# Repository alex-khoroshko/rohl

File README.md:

# Reef open hardware light
This is a project of open source / open hardware reef light. Current stage of development - proof of concept.

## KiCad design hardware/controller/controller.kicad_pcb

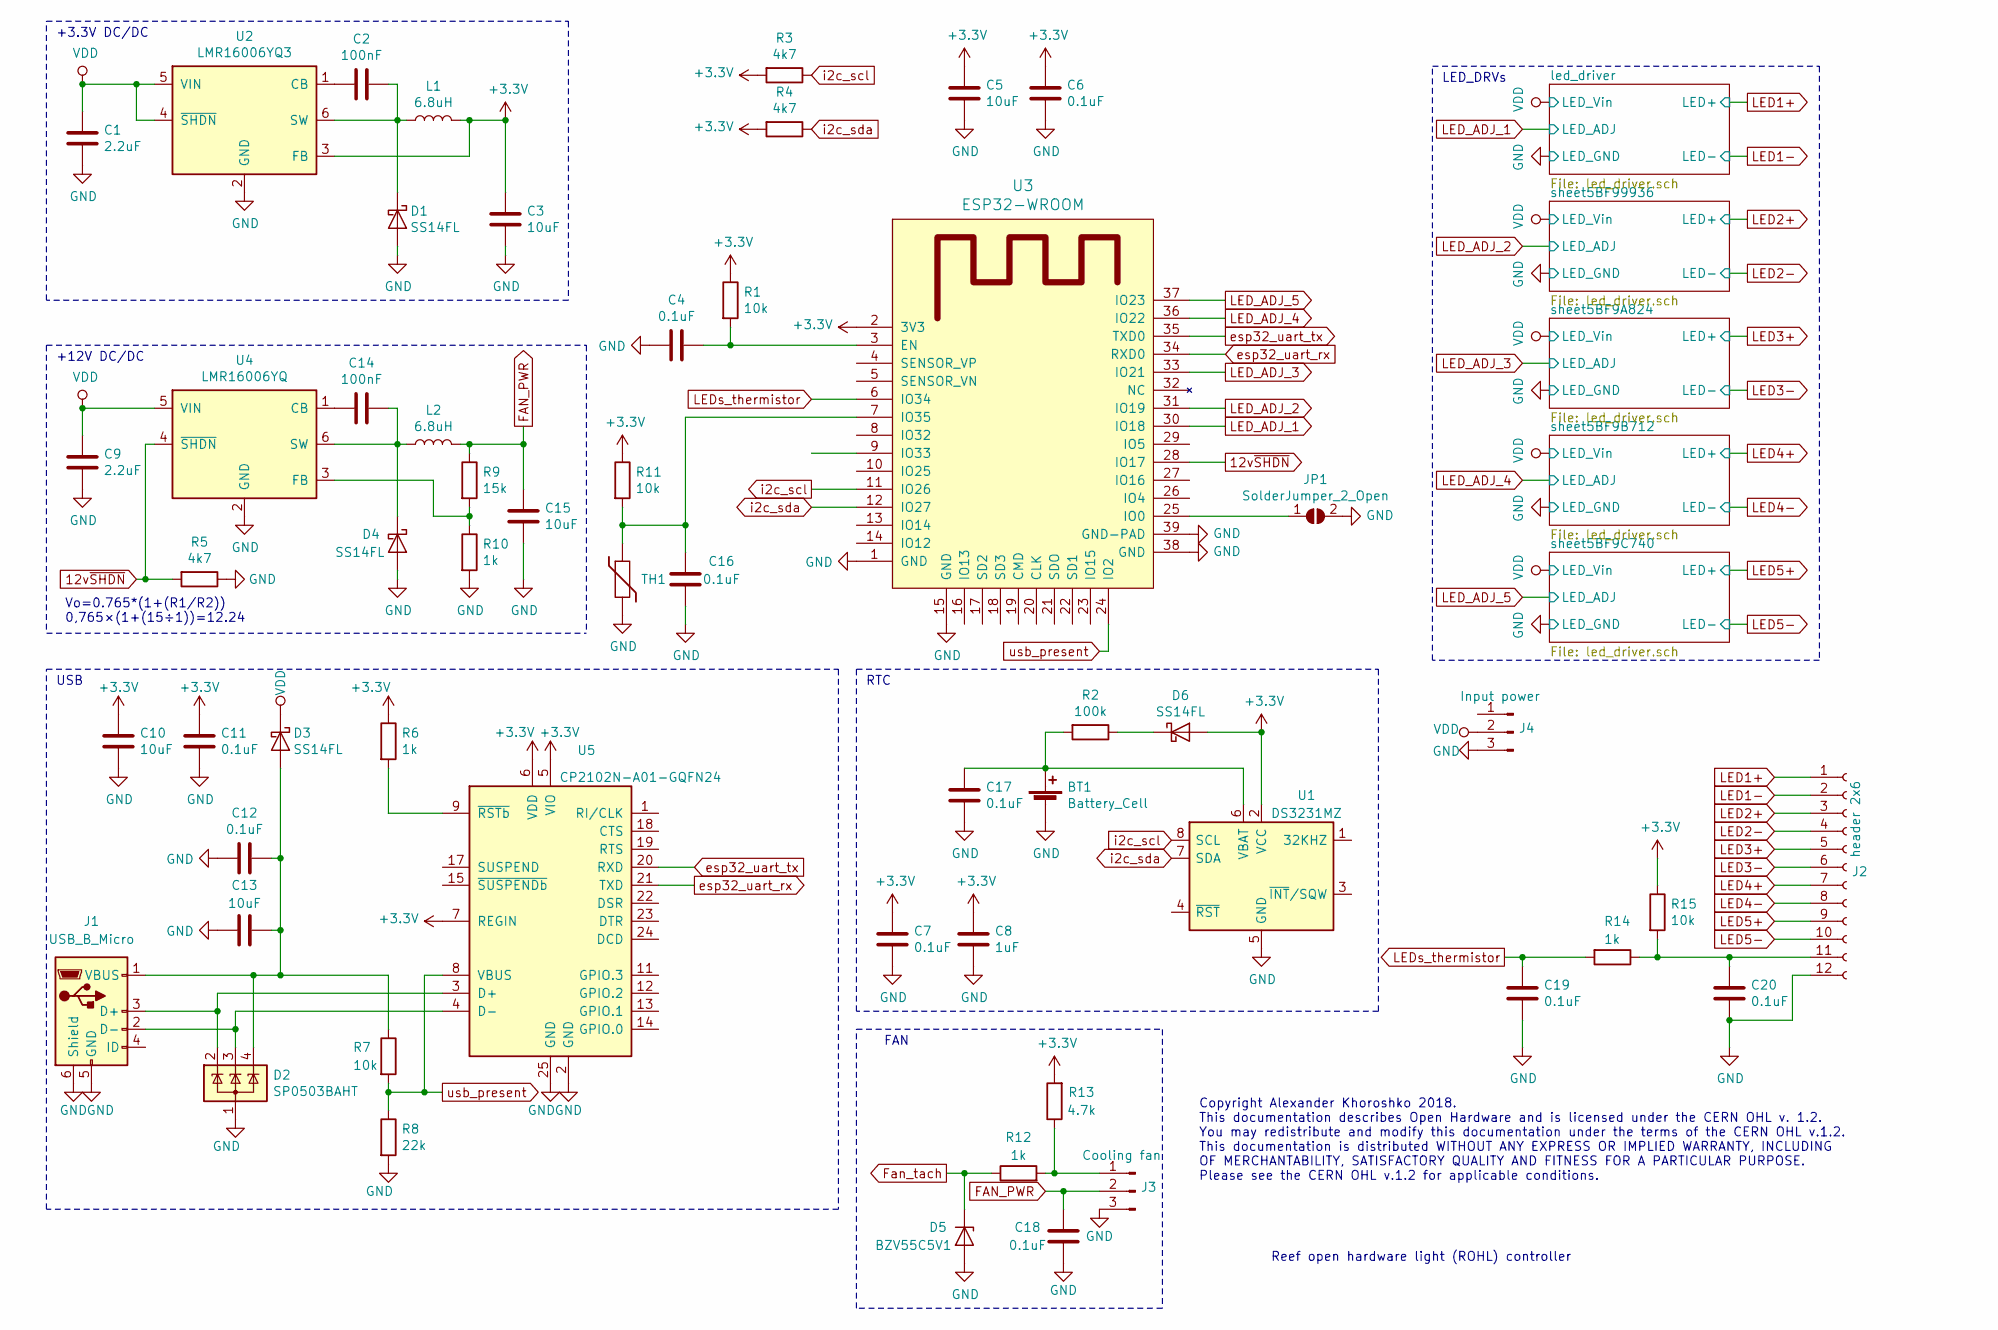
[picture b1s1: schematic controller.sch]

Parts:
BT1: Battery_Cell; MS621FE-FL11E
C1, C9: 2.2uF; C_0603_1608Metric_Pad1.05x0.95mm_HandSolder
C2, C14: 100nF; C_0603_1608Metric_Pad1.05x0.95mm_HandSolder
C3, C5, C10, C13, C15: 10uF; C_0603_1608Metric_Pad1.05x0.95mm_HandSolder
C4, C6, C7, C11, C12, C16, C17, C18, C19, C20: 0.1uF; C_0603_1608Metric_Pad1.05x0.95mm_HandSolder
C8: 1uF; C_0603_1608Metric_Pad1.05x0.95mm_HandSolder
D1, D3, D4, D6: SS14FL; D_SOD-123F
D2: SP0503BAHT; SOT-143
D5: BZV55C5V1; D_MiniMELF
J1: USB_B_Micro; USB_Micro-B_Molex-105017-0001
J2: header 2x6; PinHeader_2x06_P2.54mm_Vertical
J3: Cooling fan; FanPinHeader_1x03_P2.54mm_Vertical
J4: Input power; FanPinHeader_1x03_P2.54mm_Vertical
JP1: SolderJumper_2_Open; SolderJumper-2_P1.3mm_Open_TrianglePad1.0x1.5mm
L1, L2: 6.8uH; L_Wuerth_MAPI-3015
R1, R7, R11, R15: 10k; R_0603_1608Metric_Pad1.05x0.95mm_HandSolder
R2: 100k; R_0603_1608Metric_Pad1.05x0.95mm_HandSolder
R3, R4, R5: 4k7; R_0603_1608Metric_Pad1.05x0.95mm_HandSolder
R6, R10, R12, R14: 1k; R_0603_1608Metric_Pad1.05x0.95mm_HandSolder
R8: 22k; R_0603_1608Metric_Pad1.05x0.95mm_HandSolder
R9: 15k; R_0603_1608Metric_Pad1.05x0.95mm_HandSolder
R13: 4.7k; R_0603_1608Metric_Pad1.05x0.95mm_HandSolder
TH1: NTCS0603E3103; R_0603_1608Metric_Pad1.05x0.95mm_HandSolder
U1: DS3231MZ; SOIC-8_3.9x4.9mm_P1.27mm
U2: LMR16006YQ3; SOT-23-6
U3: ESP32-WROOM
U4: LMR16006YQ; SOT-23-6
U5: CP2102N-A01-GQFN24; QFN-24-1EP_4x4mm_P0.5mm_EP2.6x2.6mm

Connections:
12v~SHDN: R5.2, U3.28 (IO17), U4.4 (~SHDN)
+3V3: C3.1, C5.1, C6.2, C7.2, C8.2, C10.1, C11.2, D6.2 (A), L1.2, R1.1, R3.2, R4.2, R6.1, R11.1, R13.2, R15.1, U1.2 (VCC), U2.3 (FB), U3.2 (3V3), U5.5 (VIO), U5.6 (VDD), U5.7 (REGIN)
FAN_PWR: C15.1, C18.2, J3.2, L2.2, R9.1
Fan_tach: D5.1 (K), R12.1
GND: BT1.2 (-), C1.2, C3.2, C4.2, C5.2, C6.1, C7.1, C8.1, C9.2, C10.2, C11.1, C12.1, C13.2, C15.2, C16.1, C17.1, C18.1, C19.1, C20.1, D1.2 (A), D2.1 (A), D4.2 (A), D5.2 (A), J1.5 (GND), J1.6 (Shield), J2.12, J3.3, J4.3, JP1.2 (B), R5.1, R8.2, R10.2, TH1.2, U1.5 (GND), U2.2 (GND), U3.1 (GND), U3.15 (GND), U3.38 (GND), U3.39 (GND-PAD), U4.2 (GND), U5.2 (GND), U5.25 (GND); also elsewhere on the board
LED1+: J2.1; also elsewhere on the board
LED1-: J2.2; also elsewhere on the board
LED2+: J2.3; also elsewhere on the board
LED2-: J2.4; also elsewhere on the board
LED3+: J2.5; also elsewhere on the board
LED3-: J2.6; also elsewhere on the board
LED4+: J2.7; also elsewhere on the board
LED4-: J2.8; also elsewhere on the board
LED5+: J2.9; also elsewhere on the board
LED5-: J2.10; also elsewhere on the board
LED_ADJ_1: U3.30 (IO18); also elsewhere on the board
LED_ADJ_2: U3.31 (IO19); also elsewhere on the board
LED_ADJ_3: U3.33 (IO21); also elsewhere on the board
LED_ADJ_4: U3.36 (IO22); also elsewhere on the board
LED_ADJ_5: U3.37 (IO23); also elsewhere on the board
LEDs_thermistor: C19.2, R14.2, U3.6 (IO34)
unnamed: BT1.1 (+), C17.2, R2.2, U1.6 (VBAT)
unnamed: C2.1, D1.1 (K), L1.1, U2.6 (SW)
unnamed: C2.2, U2.1 (CB)
unnamed: C4.1, R1.2, U3.3 (EN)
unnamed: C12.2, C13.1, D2.4 (K), D3.2 (A), J1.1 (VBUS), R7.1
unnamed: C14.1, D4.1 (K), L2.1, U4.6 (SW)
unnamed: C14.2, U4.1 (CB)
unnamed: C16.2, R11.2, TH1.1, U3.7 (IO35)
unnamed: C20.2, J2.11, R14.1, R15.2
unnamed: D2.2 (K), J1.3 (D+), U5.3 (D+)
unnamed: D2.3 (K), J1.2 (D-), U5.4 (D-)
unnamed: D6.1 (K), R2.1
unnamed: J3.1, R12.2, R13.1
unnamed: JP1.1 (A), U3.25 (IO0)
unnamed: R6.2, U5.9 (~RSTb)
unnamed: R9.2, R10.1, U4.3 (FB)
VDD: C1.1, C9.1, D3.1 (K), J4.2, U2.4 (~SHDN), U2.5 (VIN), U4.5 (VIN); also elsewhere on the board
esp32_uart_rx: U3.34 (RXD0), U5.21 (TXD)
esp32_uart_tx: U3.35 (TXD0), U5.20 (RXD)
i2c_scl: R3.1, U1.8 (SCL), U3.11 (IO26)
i2c_sda: R4.1, U1.7 (SDA), U3.12 (IO27)
usb_present: R7.2, R8.1, U3.24 (IO2), U5.8 (VBUS)

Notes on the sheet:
RTC
+3.3V DC/DC
USB
LED_DRVs
+12V DC/DC
FAN
Vo=0.765*(1+(R1/R2)) 0,765×(1+(15÷1))=12.24
Copyright Alexander Khoroshko 2018. This documentation describes Open Hardware and is licensed under the CERN OHL v. 1.2. You may redistribute and modify this documentation under the terms of the CERN OHL v.1.2. This documentation is distributed WITHOUT ANY EXPRESS OR IMPLIED WARRANTY, INCLUDING OF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
Reef open hardware light (ROHL) controller

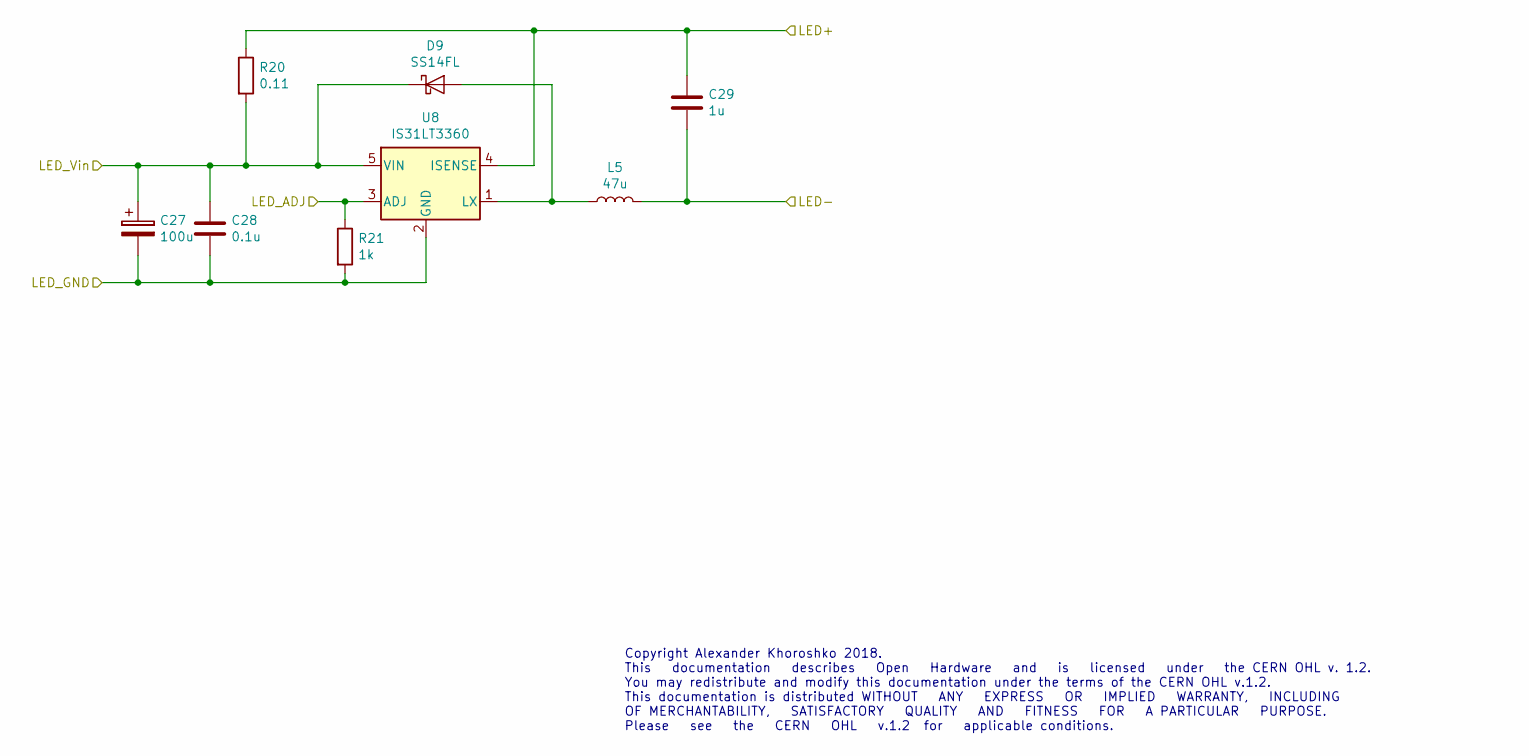
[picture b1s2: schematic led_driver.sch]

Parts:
C21: 100u; CP_Elec_10x7.9
C22: 0.1u; C_0603_1608Metric_Pad1.05x0.95mm_HandSolder
C23: 1u; C_0603_1608Metric_Pad1.05x0.95mm_HandSolder
D7: SS14FL; D_SOD-123F
L3: 47u; L_12x12mm_H6mm
R16: 0.11; R_0805_2012Metric_Pad1.15x1.40mm_HandSolder
R17: 1k; R_0603_1608Metric_Pad1.05x0.95mm_HandSolder
U6: IS31LT3360; SOT-89-5

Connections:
GND: C21.2, C22.2, R17.2, U6.2 (GND); also elsewhere on the board
LED1+: C23.1, R16.1, U6.4 (ISENSE); also elsewhere on the board
LED1-: C23.2, L3.2; also elsewhere on the board
LED_ADJ_1: R17.1, U6.3 (ADJ); also elsewhere on the board
unnamed: D7.2 (A), L3.1, U6.1 (LX)
VDD: C21.1, C22.1, D7.1 (K), R16.2, U6.5 (VIN); also elsewhere on the board

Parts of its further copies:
C24, C27, C30, C33: 100u; CP_Elec_10x7.9
C25, C28, C31, C34: 0.1u; C_0603_1608Metric_Pad1.05x0.95mm_HandSolder
C26, C29, C32, C35: 1u; C_0603_1608Metric_Pad1.05x0.95mm_HandSolder
D8, D9, D10, D11: SS14FL; D_SOD-123F
L4, L5, L6, L7: 47u; L_12x12mm_H6mm
R18, R20, R22, R24: 0.11; R_0805_2012Metric_Pad1.15x1.40mm_HandSolder
R19, R21, R23, R25: 1k; R_0603_1608Metric_Pad1.05x0.95mm_HandSolder
U7, U8, U9, U10: IS31LT3360; SOT-89-5

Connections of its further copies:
GND: C24.2, C25.2, C27.2, C28.2, C30.2, C31.2, C33.2, C34.2, R19.2, R21.2, R23.2, R25.2, U7.2 (GND), U8.2 (GND), U9.2 (GND), U10.2 (GND); also elsewhere on the board
LED2+: C26.1, R18.1, U7.4 (ISENSE); also elsewhere on the board
LED2-: C26.2, L4.2; also elsewhere on the board
LED3+: C29.1, R20.1, U8.4 (ISENSE); also elsewhere on the board
LED3-: C29.2, L5.2; also elsewhere on the board
LED4+: C32.1, R22.1, U9.4 (ISENSE); also elsewhere on the board
LED4-: C32.2, L6.2; also elsewhere on the board
LED5+: C35.1, R24.1, U10.4 (ISENSE); also elsewhere on the board
LED5-: C35.2, L7.2; also elsewhere on the board
LED_ADJ_2: R19.1, U7.3 (ADJ); also elsewhere on the board
LED_ADJ_3: R21.1, U8.3 (ADJ); also elsewhere on the board
LED_ADJ_4: R23.1, U9.3 (ADJ); also elsewhere on the board
LED_ADJ_5: R25.1, U10.3 (ADJ); also elsewhere on the board
unnamed: D8.2 (A), L4.1, U7.1 (LX)
unnamed: D9.2 (A), L5.1, U8.1 (LX)
unnamed: D10.2 (A), L6.1, U9.1 (LX)
unnamed: D11.2 (A), L7.1, U10.1 (LX)
VDD: C24.1, C25.1, C27.1, C28.1, C30.1, C31.1, C33.1, C34.1, D8.1 (K), D9.1 (K), D10.1 (K), D11.1 (K), R18.2, R20.2, R22.2, R24.2, U7.5 (VIN), U8.5 (VIN), U9.5 (VIN), U10.5 (VIN); also elsewhere on the board

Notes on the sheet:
Copyright Alexander Khoroshko 2018. This documentation describes Open Hardware and is licensed under the CERN OHL v. 1.2. You may redistribute and modify this documentation under the terms of the CERN OHL v.1.2. This documentation is distributed WITHOUT ANY EXPRESS OR IMPLIED WARRANTY, INCLUDING OF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

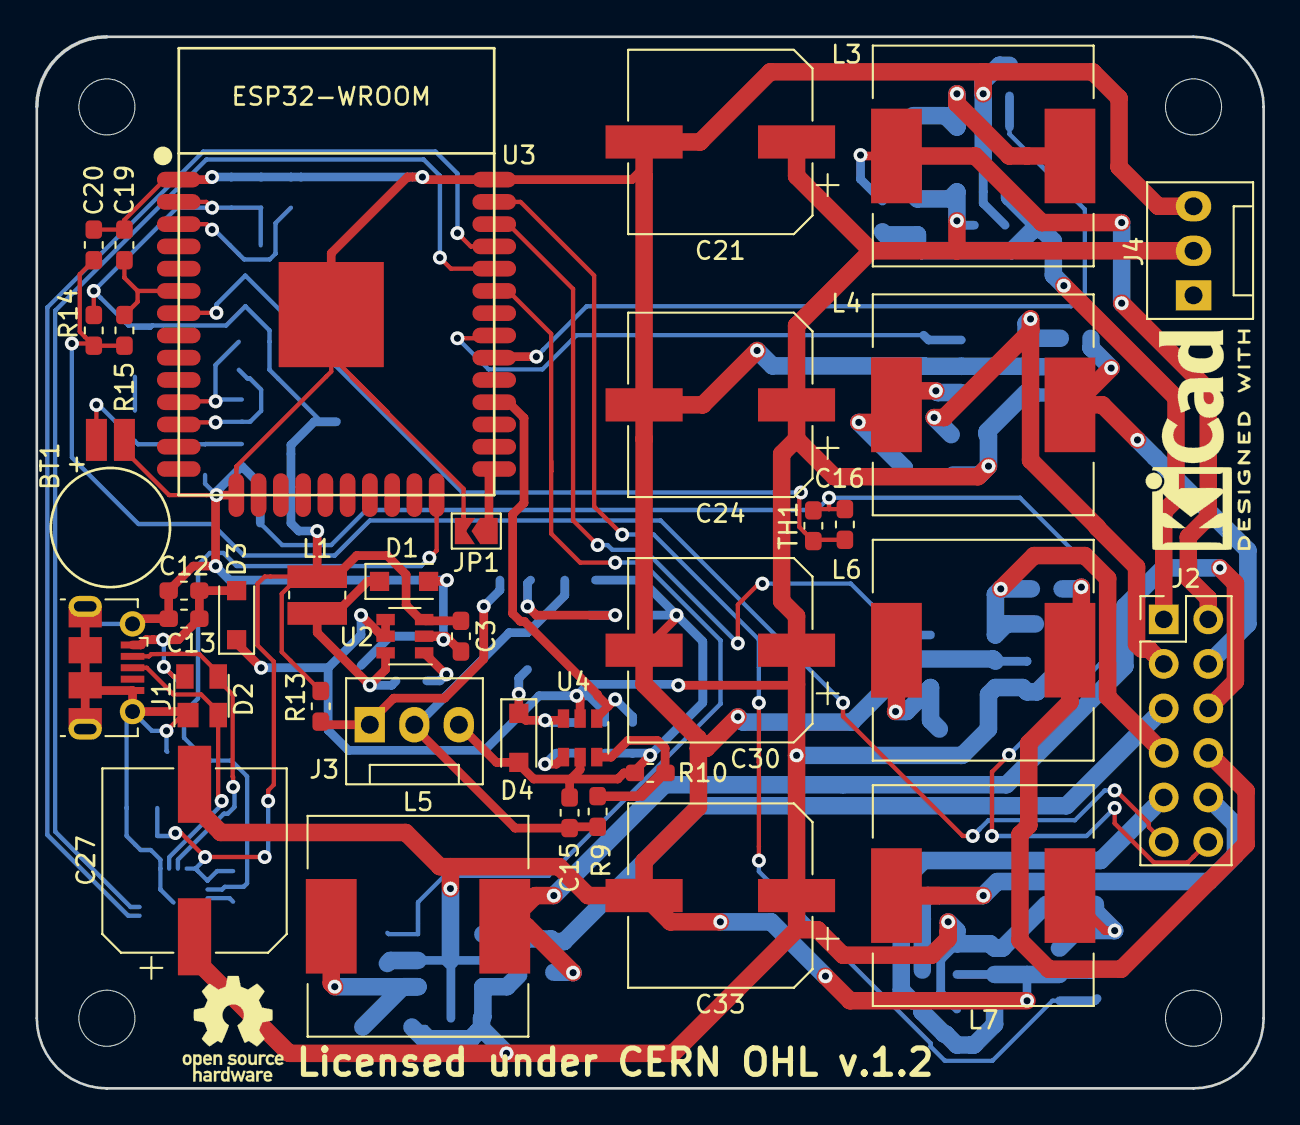
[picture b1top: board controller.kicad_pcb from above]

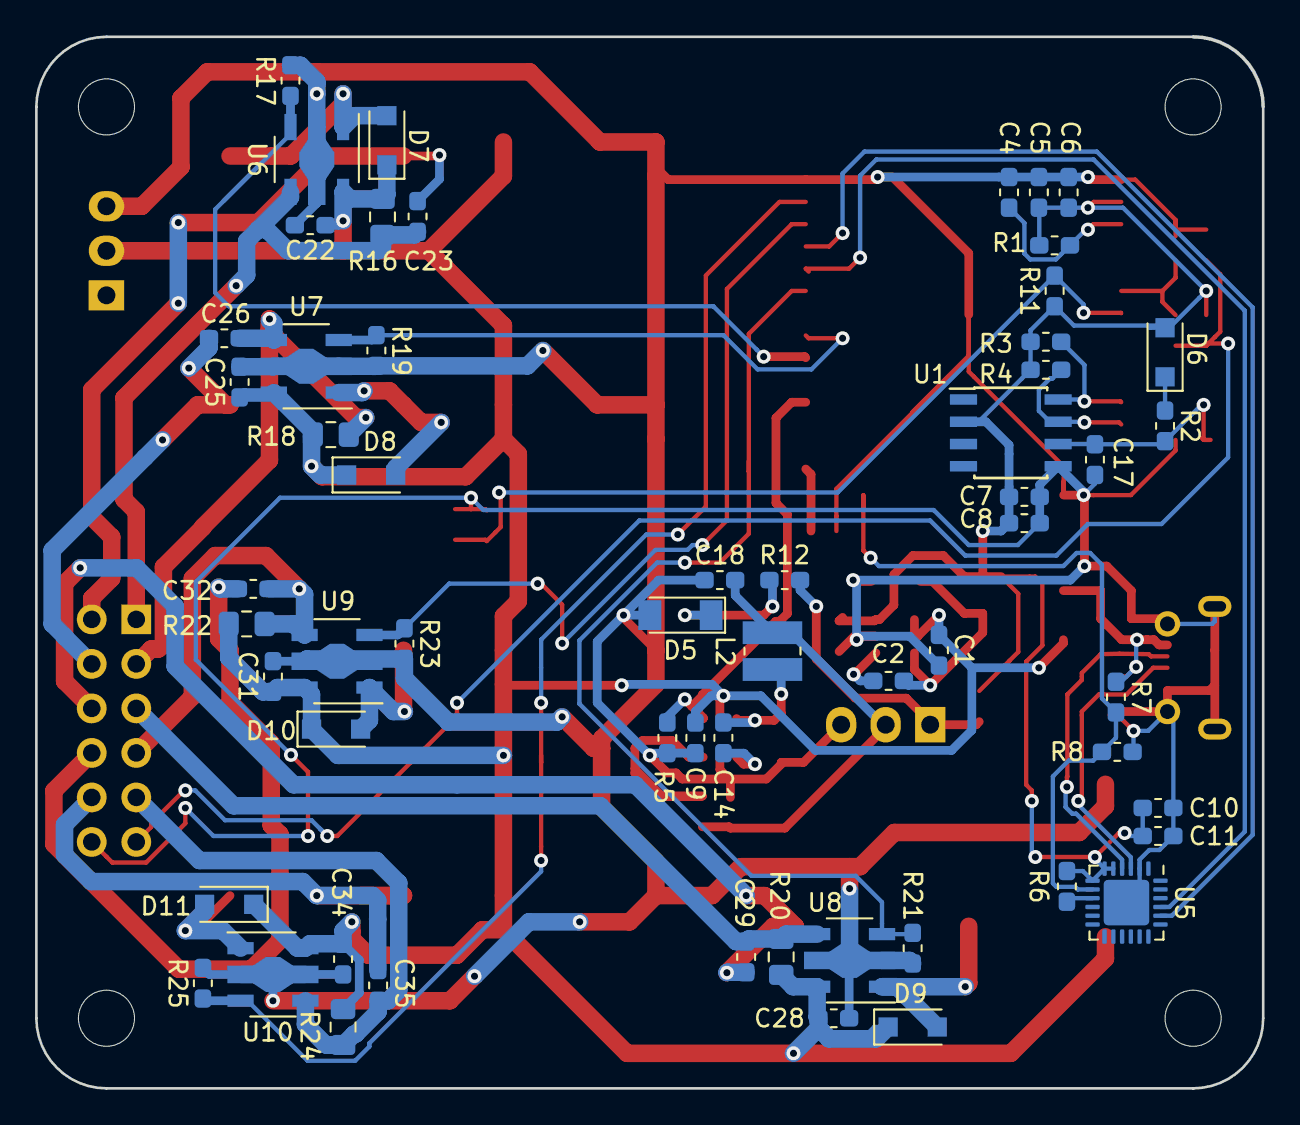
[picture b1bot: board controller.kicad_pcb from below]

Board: 2 copper layers, 70.0 x 60.0 mm, 95 parts (58 on the bottom side), 48 nets.

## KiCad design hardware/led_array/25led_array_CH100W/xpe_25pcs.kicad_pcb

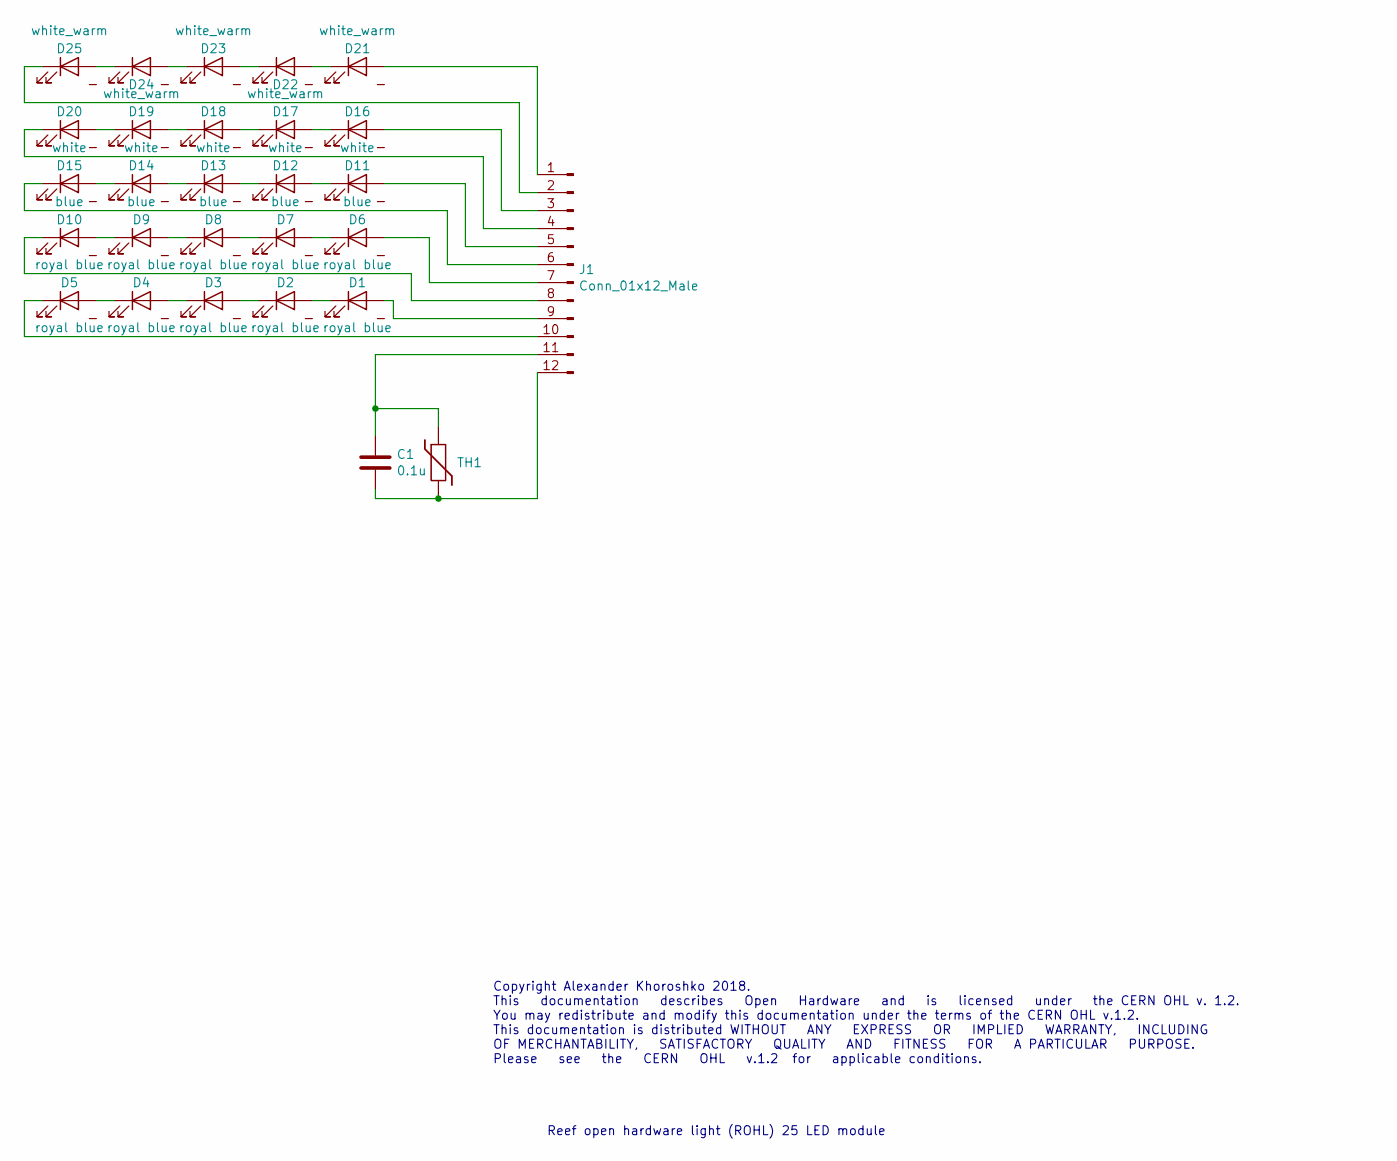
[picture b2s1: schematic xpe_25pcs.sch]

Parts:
C1: 0.1u; C_0603_1608Metric_Pad1.05x0.95mm_HandSolder
D1, D2, D3, D4, D5, D6, D7, D8, D9, D10: royal blue; LED_Cree-XP-E
D11, D12, D13, D14, D15: blue; LED_Cree-XP-E
D16, D17, D18, D19, D20: white; LED_Cree-XP-E
D21, D22, D23, D24, D25: white_warm; LED_Cree-XP-E
J1: Conn_01x12_Male; header_12_smd
TH1: NTCS0603E3103; C_0603_1608Metric_Pad1.05x0.95mm_HandSolder

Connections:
unnamed: C1.1, J1.11, TH1.1
unnamed: C1.2, J1.12, TH1.2
unnamed: D1.1 (K), D2.2 (A)
unnamed: D1.2 (A), J1.9
unnamed: D2.1 (K), D3.2 (A)
unnamed: D3.1 (K), D4.2 (A)
unnamed: D4.1 (K), D5.2 (A)
unnamed: D5.1 (K), J1.10
unnamed: D6.1 (K), D7.2 (A)
unnamed: D6.2 (A), J1.7
unnamed: D7.1 (K), D8.2 (A)
unnamed: D8.1 (K), D9.2 (A)
unnamed: D10.1 (K), J1.8
unnamed: D9.1 (K), D10.2 (A)
unnamed: D11.1 (K), D12.2 (A)
unnamed: D11.2 (A), J1.5
unnamed: D12.1 (K), D13.2 (A)
unnamed: D13.1 (K), D14.2 (A)
unnamed: D14.1 (K), D15.2 (A)
unnamed: D15.1 (K), J1.6
unnamed: D16.1 (K), D17.2 (A)
unnamed: D16.2 (A), J1.3
unnamed: D17.1 (K), D18.2 (A)
unnamed: D18.1 (K), D19.2 (A)
unnamed: D19.1 (K), D20.2 (A)
unnamed: D20.1 (K), J1.4
unnamed: D21.1 (K), D22.2 (A)
unnamed: D21.2 (A), J1.1
unnamed: D22.1 (K), D23.2 (A)
unnamed: D23.1 (K), D24.2 (A)
unnamed: D24.1 (K), D25.2 (A)
unnamed: D25.1 (K), J1.2
p: D1.3 (pad), D2.3 (pad), D3.3 (pad), D4.3 (pad), D5.3 (pad), D6.3 (pad), D7.3 (pad), D8.3 (pad), D9.3 (pad), D10.3 (pad), D11.3 (pad), D12.3 (pad), D13.3 (pad), D14.3 (pad), D15.3 (pad), D16.3 (pad), D17.3 (pad), D18.3 (pad), D19.3 (pad), D20.3 (pad), D21.3 (pad), D22.3 (pad), D23.3 (pad), D24.3 (pad), D25.3 (pad)

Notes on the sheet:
Copyright Alexander Khoroshko 2018. This documentation describes Open Hardware and is licensed under the CERN OHL v. 1.2. You may redistribute and modify this documentation under the terms of the CERN OHL v.1.2. This documentation is distributed WITHOUT ANY EXPRESS OR IMPLIED WARRANTY, INCLUDING OF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
Reef open hardware light (ROHL) 25 LED module

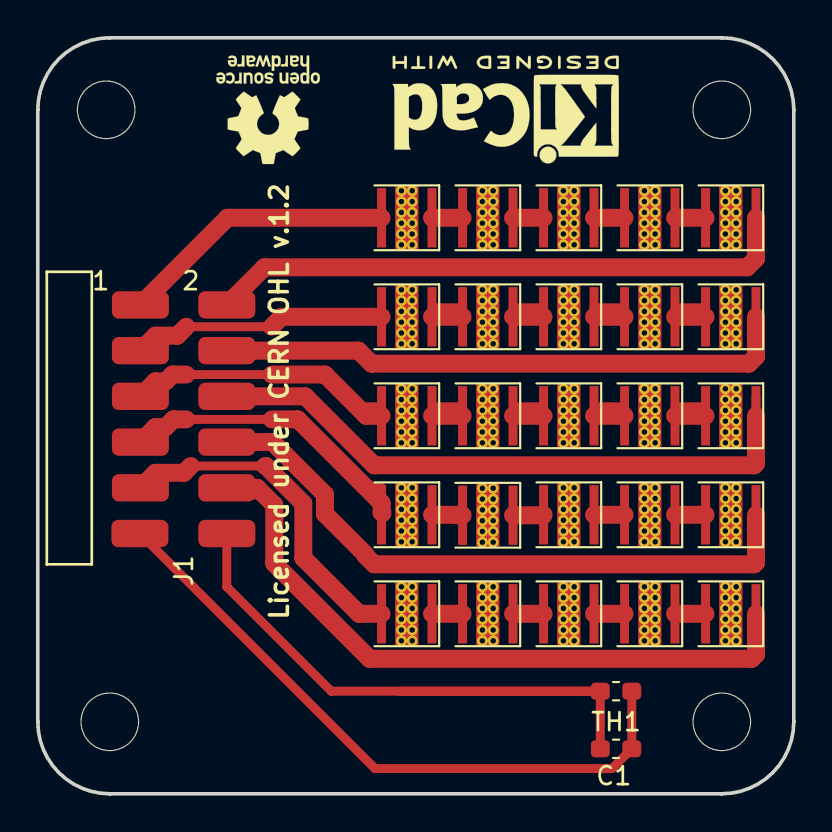
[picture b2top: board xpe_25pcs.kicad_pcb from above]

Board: 2 copper layers, 42.0 x 42.0 mm, 28 parts (0 on the bottom side), 33 nets.

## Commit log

2018-11-19 developed led model and sch
2018-11-19 initial 80mm pcb draft ready
2018-11-19 25 led array improved
2018-11-19 folder name improvements
2018-11-20 led 25 array rework (fix distance from 38 to 34mm, space between header and led added)
2018-11-22 controller schematic draft finished
2018-11-22 initial controller components placement
2018-11-22 open source hardware fix
2018-11-23 controller partially traced
2018-11-26 led array rework for fr4 board
2018-11-26 controller finished. Sent both boards for manufacturing
2018-12-02 some hw polishing, software implementation started (added sliders and basic python scripts)
2018-12-02 control.py: some debug lines added (no actual debug was made)
2018-12-02 brightness upload draft added
2018-12-04 web scripts rework
2018-12-05 software: current version uploads sliders values to server side
2018-12-05 workable version under PC python
2018-12-05 rohl_control.py functionality moved to web_server.py
2018-12-05 web page now loads brightness from server on startup
2019-01-12 rtc code added
2019-01-12 time readout added to control web page
2019-01-12 added set time functionality (works!)
2019-01-13 move time to status field in progress (looks OK)
2019-01-13 time rework in progress
2019-01-13 time editing finished (ajax part not tested)
2019-01-13 telemetry move to status field finished. works.
2019-01-26 adc, pwm and file operation implemended. Tempr readout added to web
2019-01-26 temperature display works (visuals need revision)
2019-01-27 correct temperature viewing implemended
2019-01-27 hardware todo added
2019-01-30 ap starts automatically. channel 4 and 5 tied together
2019-01-30 EMC problem added to todo
2019-01-30 todo: added CP2102 removal line
2019-02-03 todo modified
2019-02-03 pwm fixed

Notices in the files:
hardware/controller/controller.kicad_pcb:
Licensed under CERN OHL v.1.2
